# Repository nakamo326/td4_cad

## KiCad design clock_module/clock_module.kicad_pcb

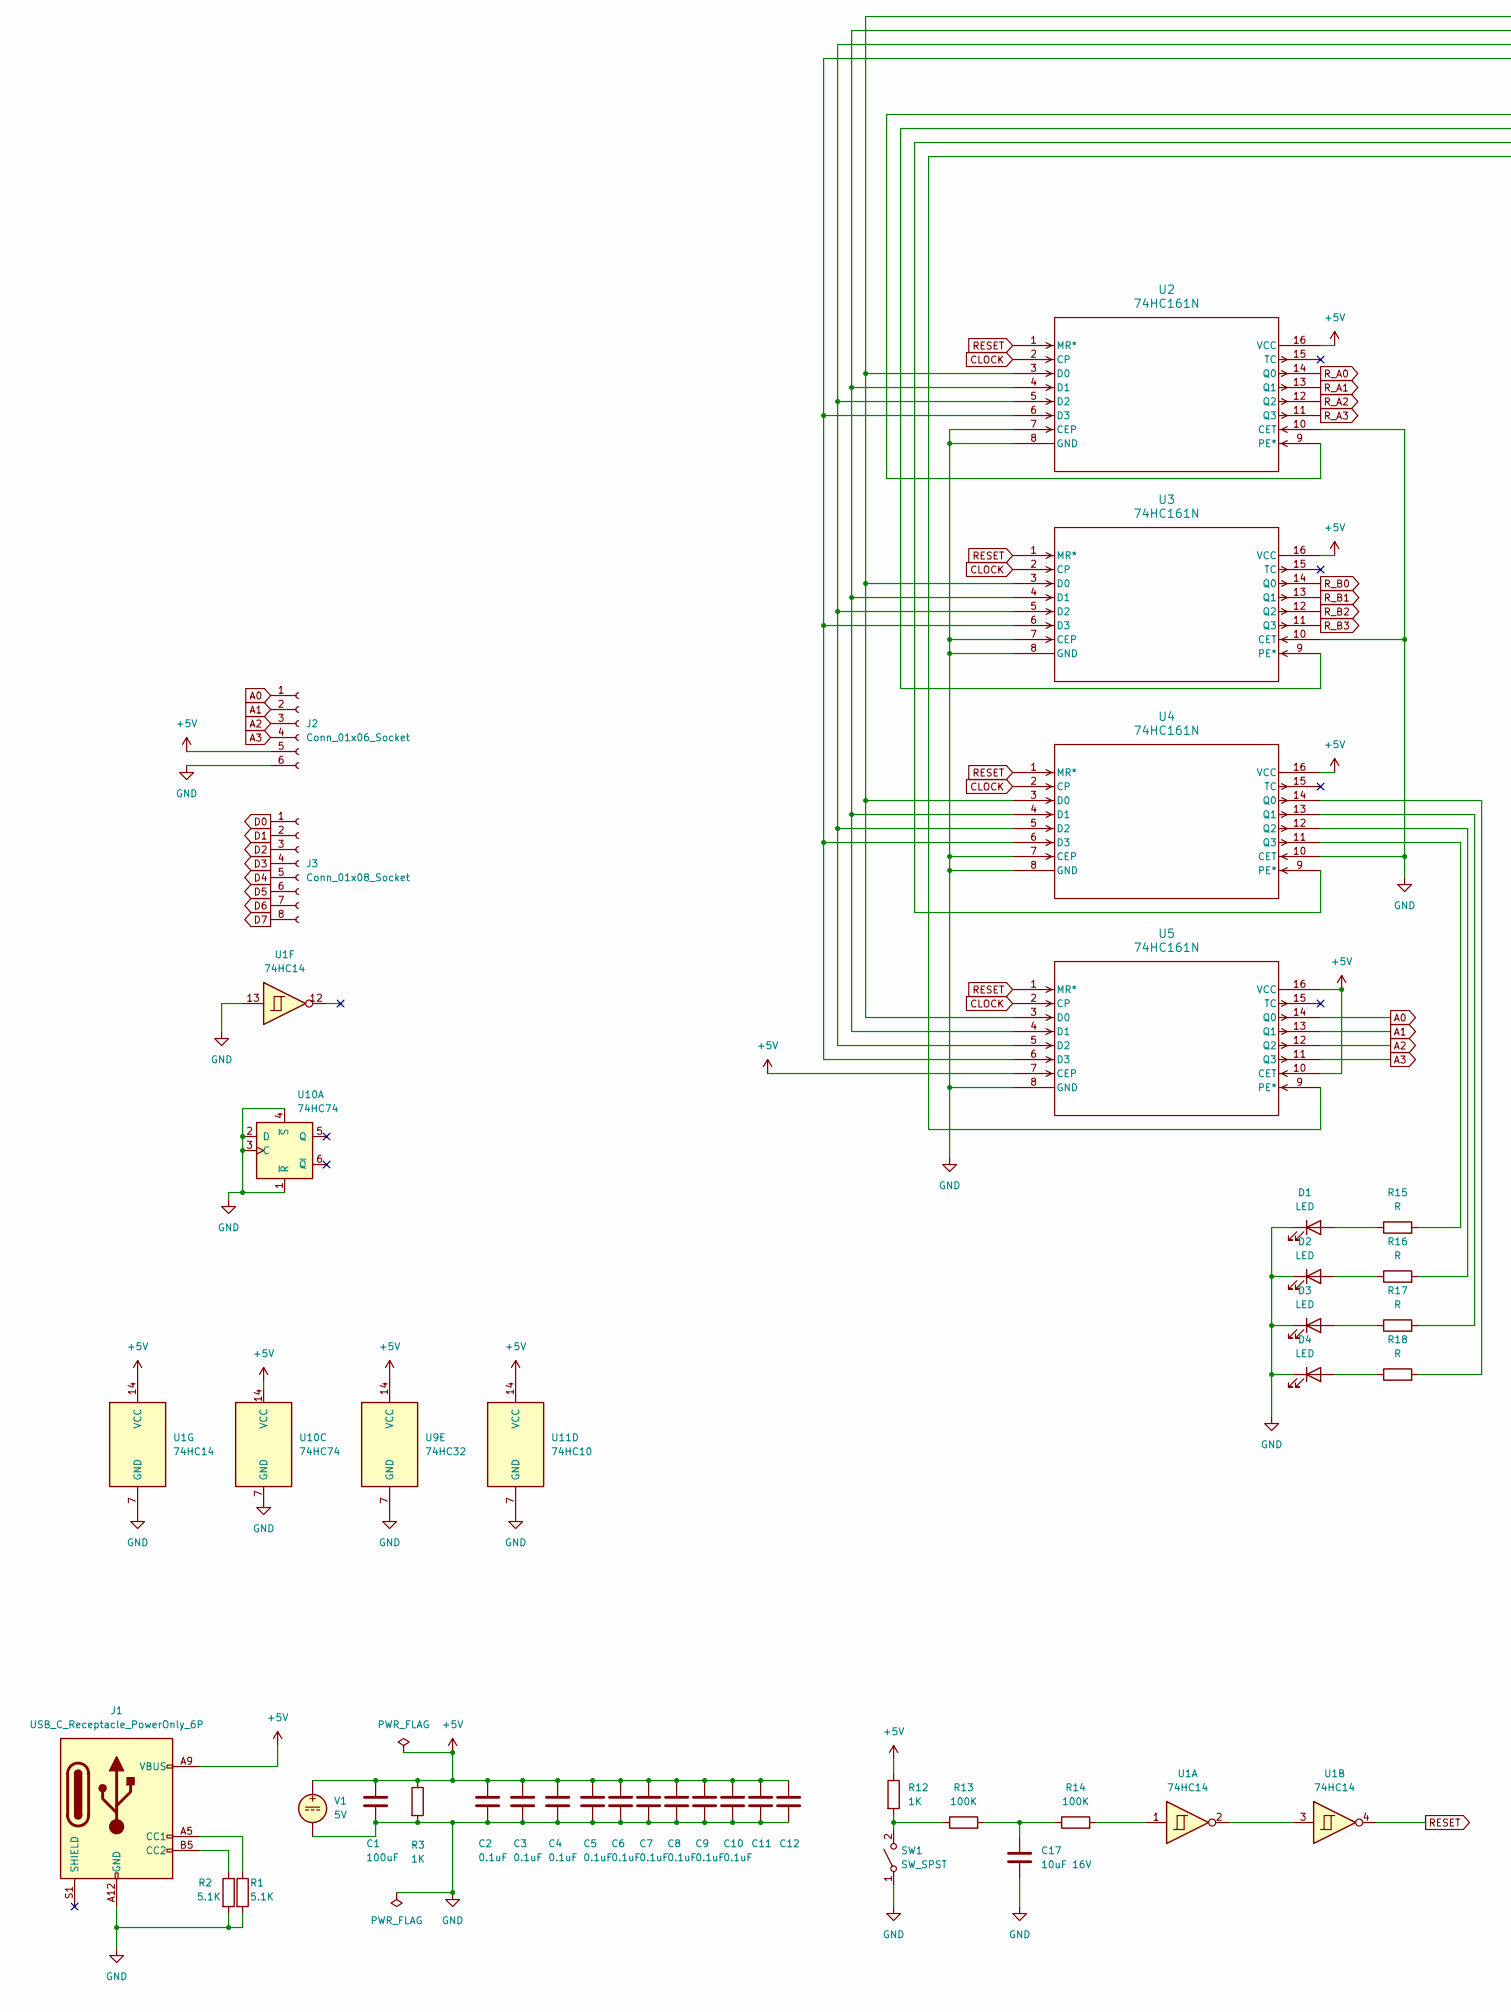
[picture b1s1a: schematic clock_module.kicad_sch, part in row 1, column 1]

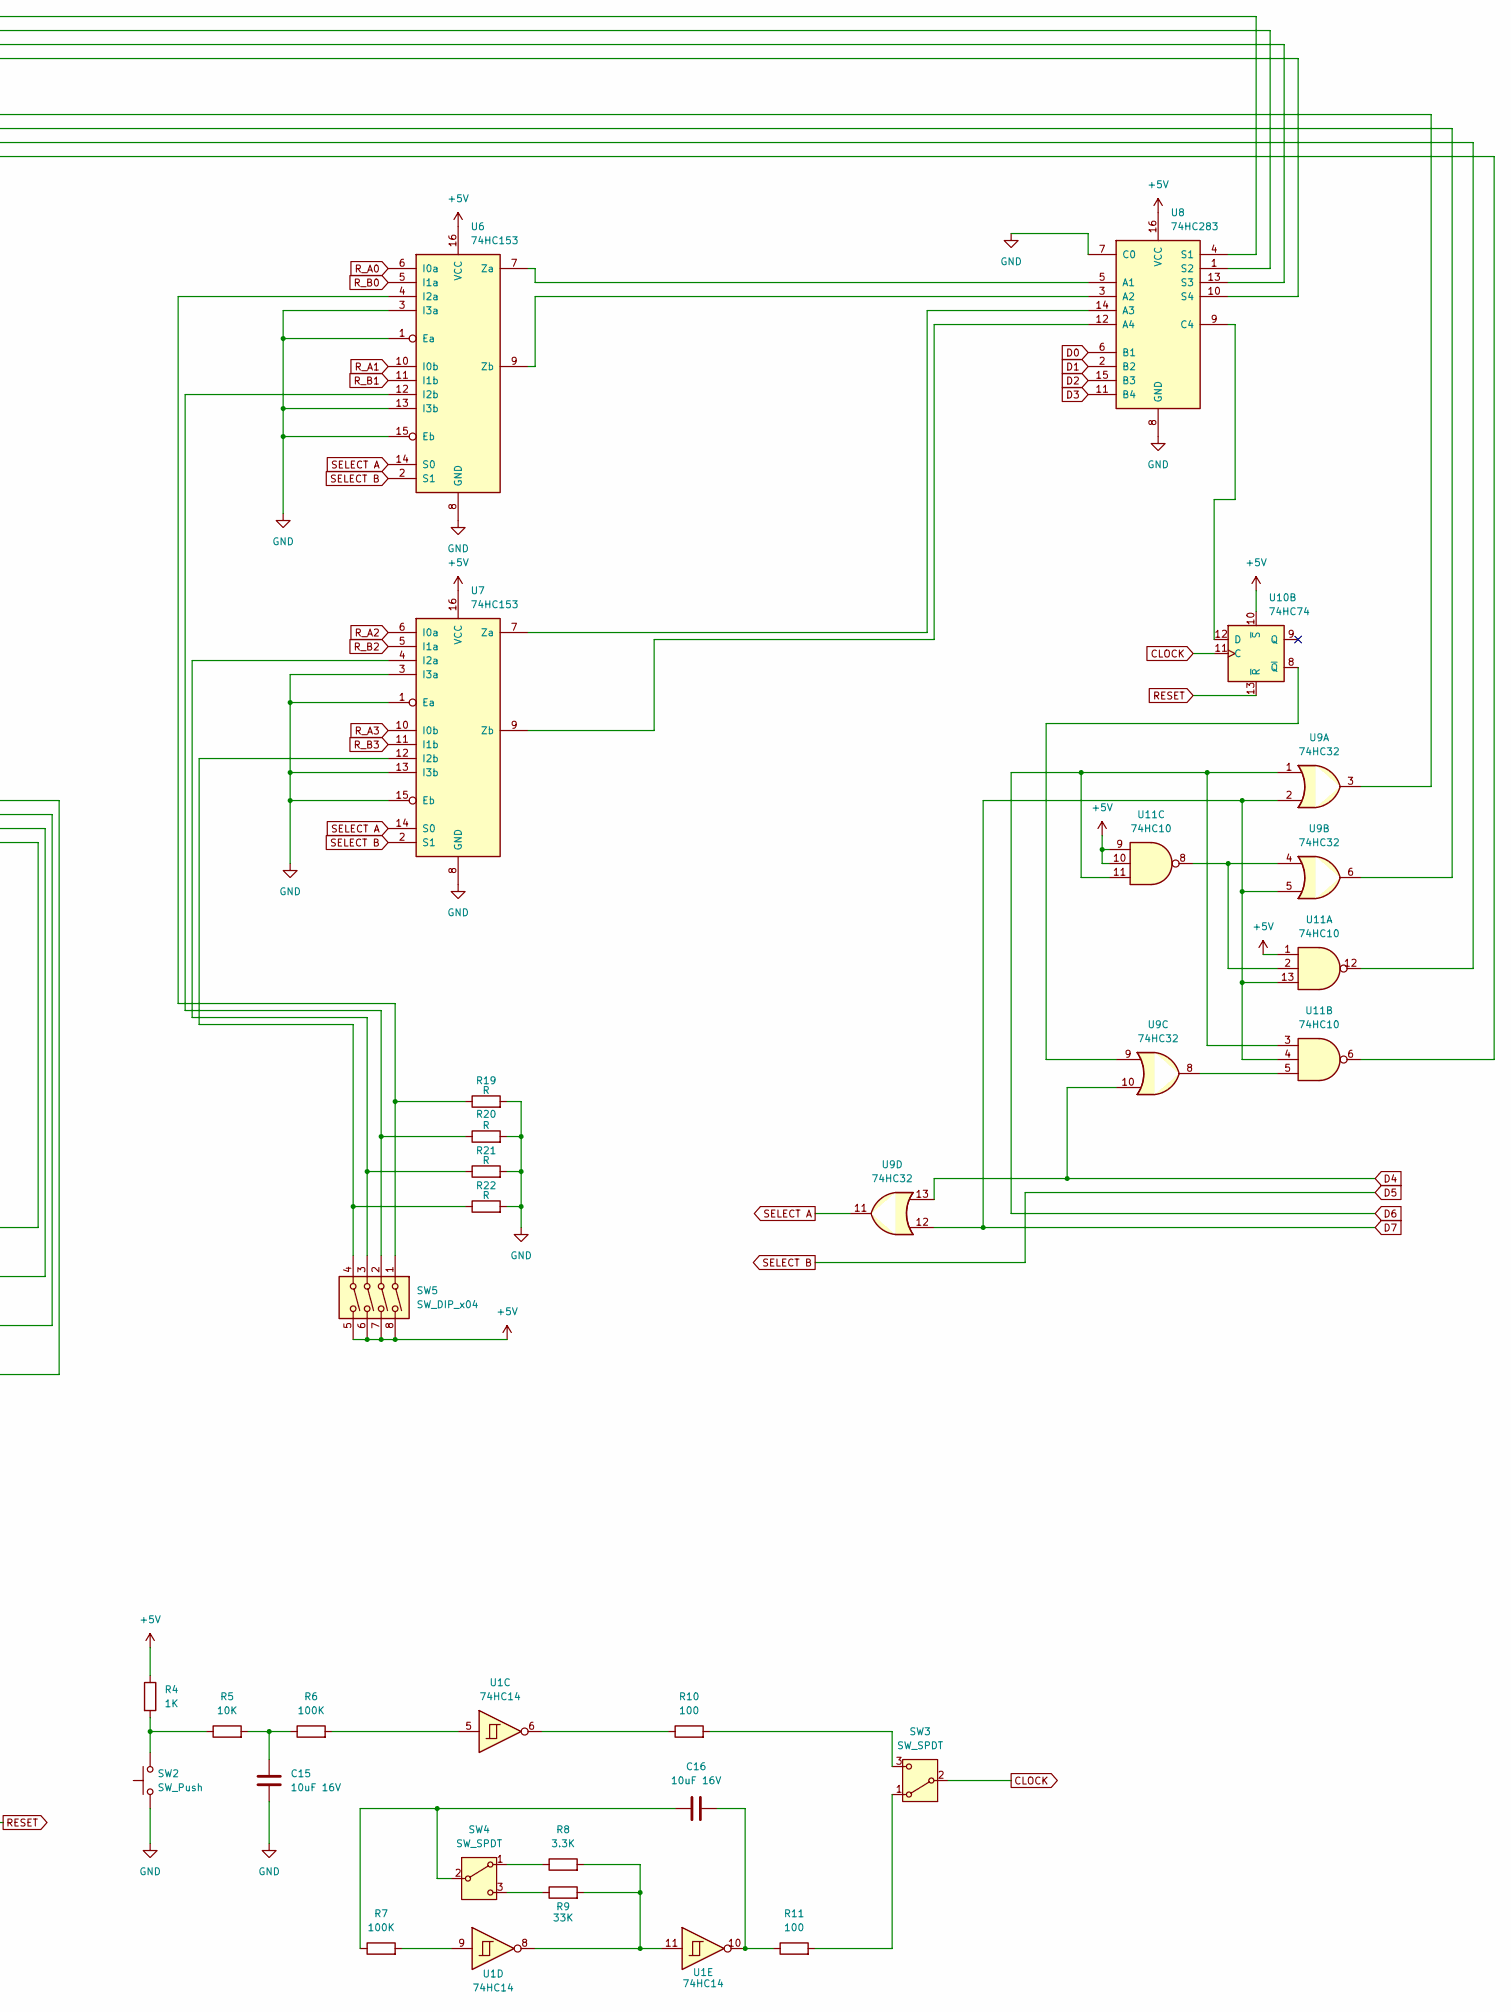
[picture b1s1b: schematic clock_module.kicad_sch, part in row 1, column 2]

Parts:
C1: 100uF; C_Disc_D4.3mm_W1.9mm_P5.00mm
C2, C3, C4, C5, C6, C7, C8, C9, C10, C11, C12: 0.1uF; C_Disc_D4.3mm_W1.9mm_P5.00mm
C15, C16, C17: 10uF 16V; C_Disc_D4.3mm_W1.9mm_P5.00mm
D1, D2, D3, D4: LED; LED_D3.0mm
J1: USB_C_Receptacle_PowerOnly_6P; UJC-HP-3-SMT-TR
J2: Conn_01x06_Socket; PinSocket_1x06_P2.54mm_Horizontal
J3: Conn_01x08_Socket; PinSocket_1x08_P2.54mm_Horizontal
R1, R2: 5.1K; R_Axial_DIN0207_L6.3mm_D2.5mm_P2.54mm_Vertical
R3, R4, R12: 1K; R_Axial_DIN0207_L6.3mm_D2.5mm_P2.54mm_Vertical
R5: 10K; R_Axial_DIN0207_L6.3mm_D2.5mm_P2.54mm_Vertical
R6, R7, R13, R14: 100K; R_Axial_DIN0207_L6.3mm_D2.5mm_P2.54mm_Vertical
R8: 3.3K; R_Axial_DIN0207_L6.3mm_D2.5mm_P2.54mm_Vertical
R9: 33K; R_Axial_DIN0207_L6.3mm_D2.5mm_P2.54mm_Vertical
R10, R11: 100; R_Axial_DIN0207_L6.3mm_D2.5mm_P2.54mm_Vertical
R15, R16, R17, R18, R19, R20, R21, R22: R; R_Axial_DIN0207_L6.3mm_D2.5mm_P2.54mm_Vertical
SW1: SW_SPST; SW_PUSH_6mm
SW2: SW_Push; SW_PUSH_6mm
SW3, SW4: SW_SPDT; SS-12D00G3
SW5: SW_DIP_x04; SW_DIP_SPSTx04_Slide_9.78x12.34mm_W7.62mm_P2.54mm
U1: 74HC14; DIP14_TOS
U2, U3, U4, U5: 74HC161N; 74hc161
U6, U7: 74HC153; SOT38-4_NEX
U8: 74HC283; 74hc283
U9: 74HC32; 74hc32
U10: 74HC74; DIP14_TOS
U11: 74HC10; 74hc10
V1: 5V

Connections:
+5V: C1.1, C2.1, C3.1, C4.1, C5.1, C6.1, C7.1, C8.1, C9.1, C10.1, C11.1, C12.1, J1.A9 (VBUS), J1.B9 (VBUS), J2.5, R3.1, R4.1, R12.1, SW5.5, SW5.6, SW5.7, SW5.8, U1.14 (VCC), U2.16 (VCC), U3.16 (VCC), U4.16 (VCC), U5.7 (CEP), U5.10 (CET), U5.16 (VCC), U6.16 (VCC), U7.16 (VCC), U8.16 (VCC), U9.14 (VCC), U10.10 (~S), U10.14 (VCC), U11.1, U11.9, U11.10, U11.14 (VCC), V1.1
A0: J2.1, U5.14 (Q0)
A1: J2.2, U5.13 (Q1)
A2: J2.3, U5.12 (Q2)
A3: J2.4, U5.11 (Q3)
CLOCK: SW3.2 (B), U2.2 (CP), U3.2 (CP), U4.2 (CP), U5.2 (CP), U10.11 (C)
D0: J3.1, U8.6 (B1)
D1: J3.2, U8.2 (B2)
D2: J3.3, U8.15 (B3)
D3: J3.4, U8.11 (B4)
D4: J3.5, U9.10, U9.13
D5: J3.6, U6.2 (S1), U7.2 (S1)
D6: J3.7, U9.1, U11.3, U11.11
D7: J3.8, U9.2, U9.5, U9.12, U11.4, U11.13
GND: C1.2, C2.2, C3.2, C4.2, C5.2, C6.2, C7.2, C8.2, C9.2, C10.2, C11.2, C12.2, C15.2, C17.2, D1.1 (K), D2.1 (K), D3.1 (K), D4.1 (K), J1.A12 (GND), J1.B12 (GND), J2.6, R1.2, R2.2, R3.2, R19.2, R20.2, R21.2, R22.2, SW1.1 (A), SW2.1, U1.7 (GND), U1.13, U2.7 (CEP), U2.8 (GND), U2.10 (CET), U3.7 (CEP), U3.8 (GND), U3.10 (CET), U4.7 (CEP), U4.8 (GND), U4.10 (CET), U5.8 (GND), U6.1 (Ea), U6.3 (I3a), U6.8 (GND), U6.13 (I3b), U6.15 (Eb), U7.1 (Ea), U7.3 (I3a), U7.8 (GND), U7.13 (I3b), U7.15 (Eb), U8.7 (C0), U8.8 (GND), U9.7 (GND), U10.1 (~R), U10.2 (D), U10.3 (C), U10.4 (~S), U10.7 (GND), U11.7 (GND), V1.2
unnamed: C15.1, R5.2, R6.1
unnamed: C16.2, R11.1, U1.10
unnamed: C17.1, R13.2, R14.1
unnamed: D1.2 (A), R15.1
unnamed: D2.2 (A), R16.1
unnamed: D3.2 (A), R17.1
unnamed: D4.2 (A), R18.1
unnamed: J1.A5 (CC1), R1.1
unnamed: J1.B5 (CC2), R2.1
unnamed: R4.2, R5.1, SW2.2
unnamed: R6.2, U1.5
unnamed: R7.2, U1.9
unnamed: R8.2, R9.2, U1.8, U1.11
unnamed: R10.1, U1.6
unnamed: R14.2, U1.1
unnamed: R12.2, R13.1, SW1.2 (B)
unnamed: R11.2, SW3.1 (A)
unnamed: R10.2, SW3.3 (C)
unnamed: R8.1, SW4.1 (A)
unnamed: C16.1, R7.1, SW4.2 (B)
unnamed: R9.1, SW4.3 (C)
unnamed: U1.2, U1.3
unnamed: U2.3 (D0), U3.3 (D0), U4.3 (D0), U5.3 (D0), U8.4 (S1)
unnamed: U2.4 (D1), U3.4 (D1), U4.4 (D1), U5.4 (D1), U8.1 (S2)
unnamed: U2.5 (D2), U3.5 (D2), U4.5 (D2), U5.5 (D2), U8.13 (S3)
unnamed: U2.6 (D3), U3.6 (D3), U4.6 (D3), U5.6 (D3), U8.10 (S4)
unnamed: U2.9 (PE*), U9.3
unnamed: U3.9 (PE*), U9.6
unnamed: U4.9 (PE*), U11.12
unnamed: R18.2, U4.14 (Q0)
unnamed: R17.2, U4.13 (Q1)
unnamed: R16.2, U4.12 (Q2)
unnamed: R15.2, U4.11 (Q3)
unnamed: U5.9 (PE*), U11.6
unnamed: R19.1, SW5.1, U6.4 (I2a)
unnamed: R20.1, SW5.2, U6.12 (I2b)
unnamed: U6.7 (Za), U8.5 (A1)
unnamed: U6.9 (Zb), U8.3 (A2)
unnamed: R21.1, SW5.3, U7.4 (I2a)
unnamed: R22.1, SW5.4, U7.12 (I2b)
unnamed: U7.7 (Za), U8.14 (A3)
unnamed: U7.9 (Zb), U8.12 (A4)
unnamed: U8.9 (C4), U10.12 (D)
unnamed: U9.9, U10.8 (~Q)
unnamed: U9.4, U11.2, U11.8
unnamed: U9.8, U11.5
RESET: U1.4, U2.1 (MR*), U3.1 (MR*), U4.1 (MR*), U5.1 (MR*), U10.13 (~R)
R_A0: U2.14 (Q0), U6.6 (I0a)
R_A1: U2.13 (Q1), U6.10 (I0b)
R_A2: U2.12 (Q2), U7.6 (I0a)
R_A3: U2.11 (Q3), U7.10 (I0b)
R_B0: U3.14 (Q0), U6.5 (I1a)
R_B1: U3.13 (Q1), U6.11 (I1b)
R_B2: U3.12 (Q2), U7.5 (I1a)
R_B3: U3.11 (Q3), U7.11 (I1b)
SELECT A: U6.14 (S0), U7.14 (S0), U9.11

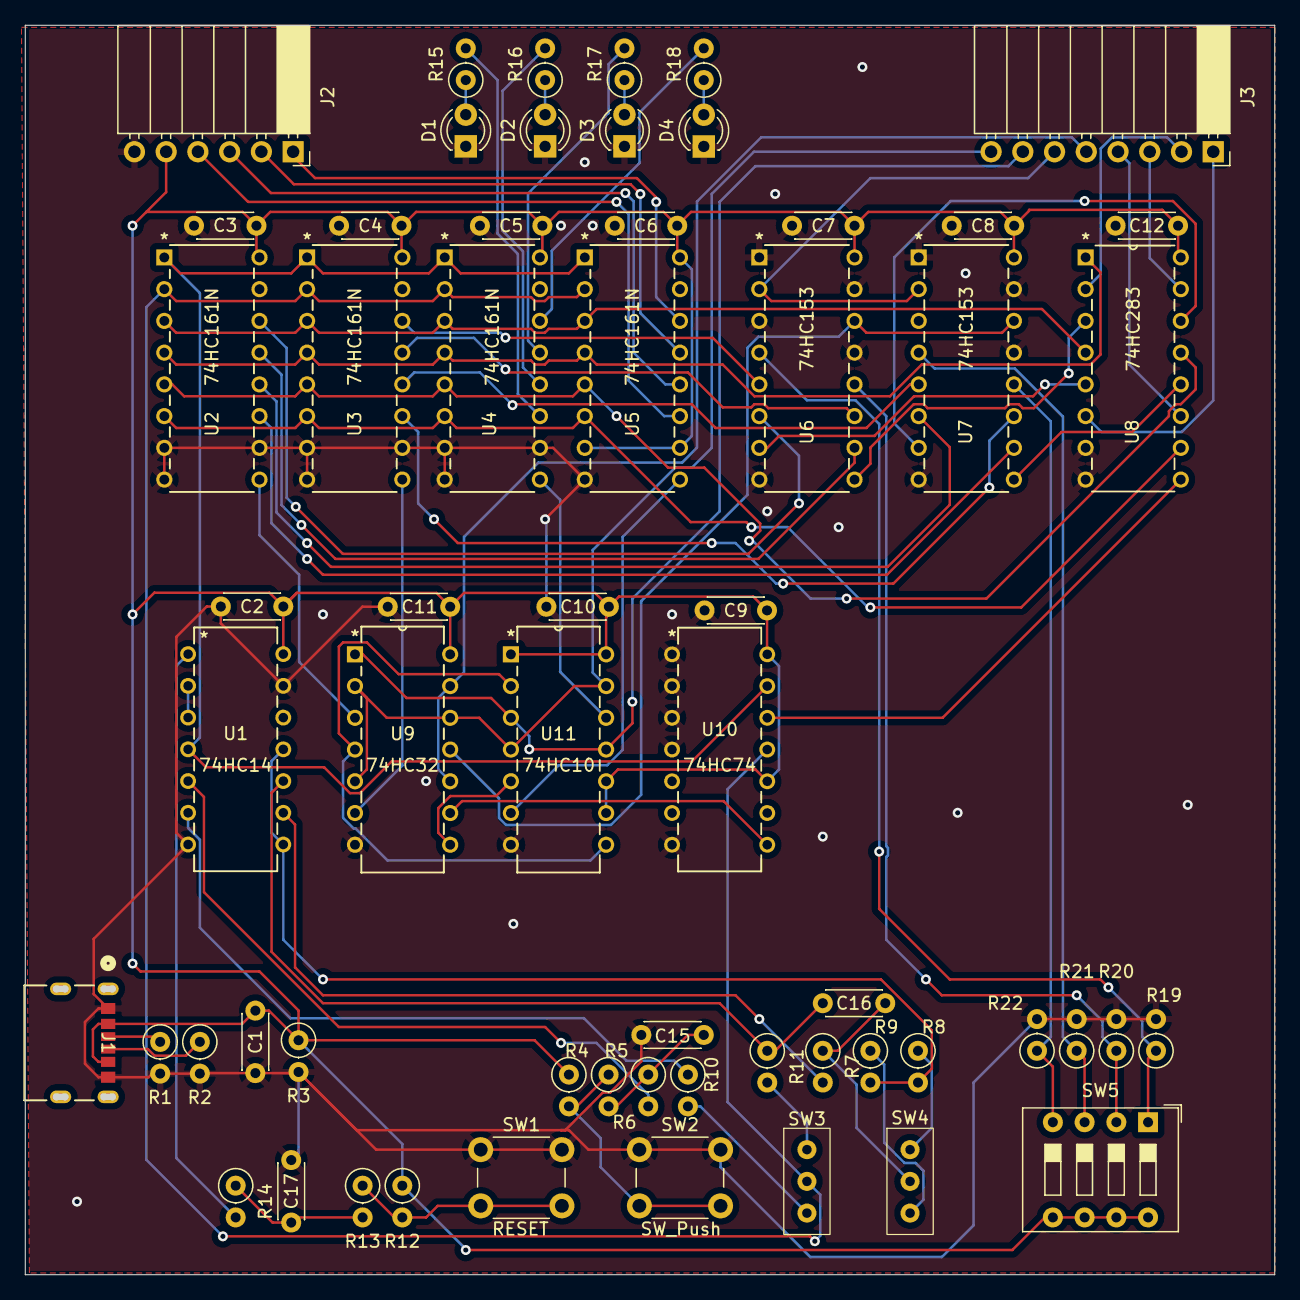
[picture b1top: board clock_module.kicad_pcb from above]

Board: 2 copper layers, 99.5 x 99.5 mm, 60 parts (0 on the bottom side), 71 nets.

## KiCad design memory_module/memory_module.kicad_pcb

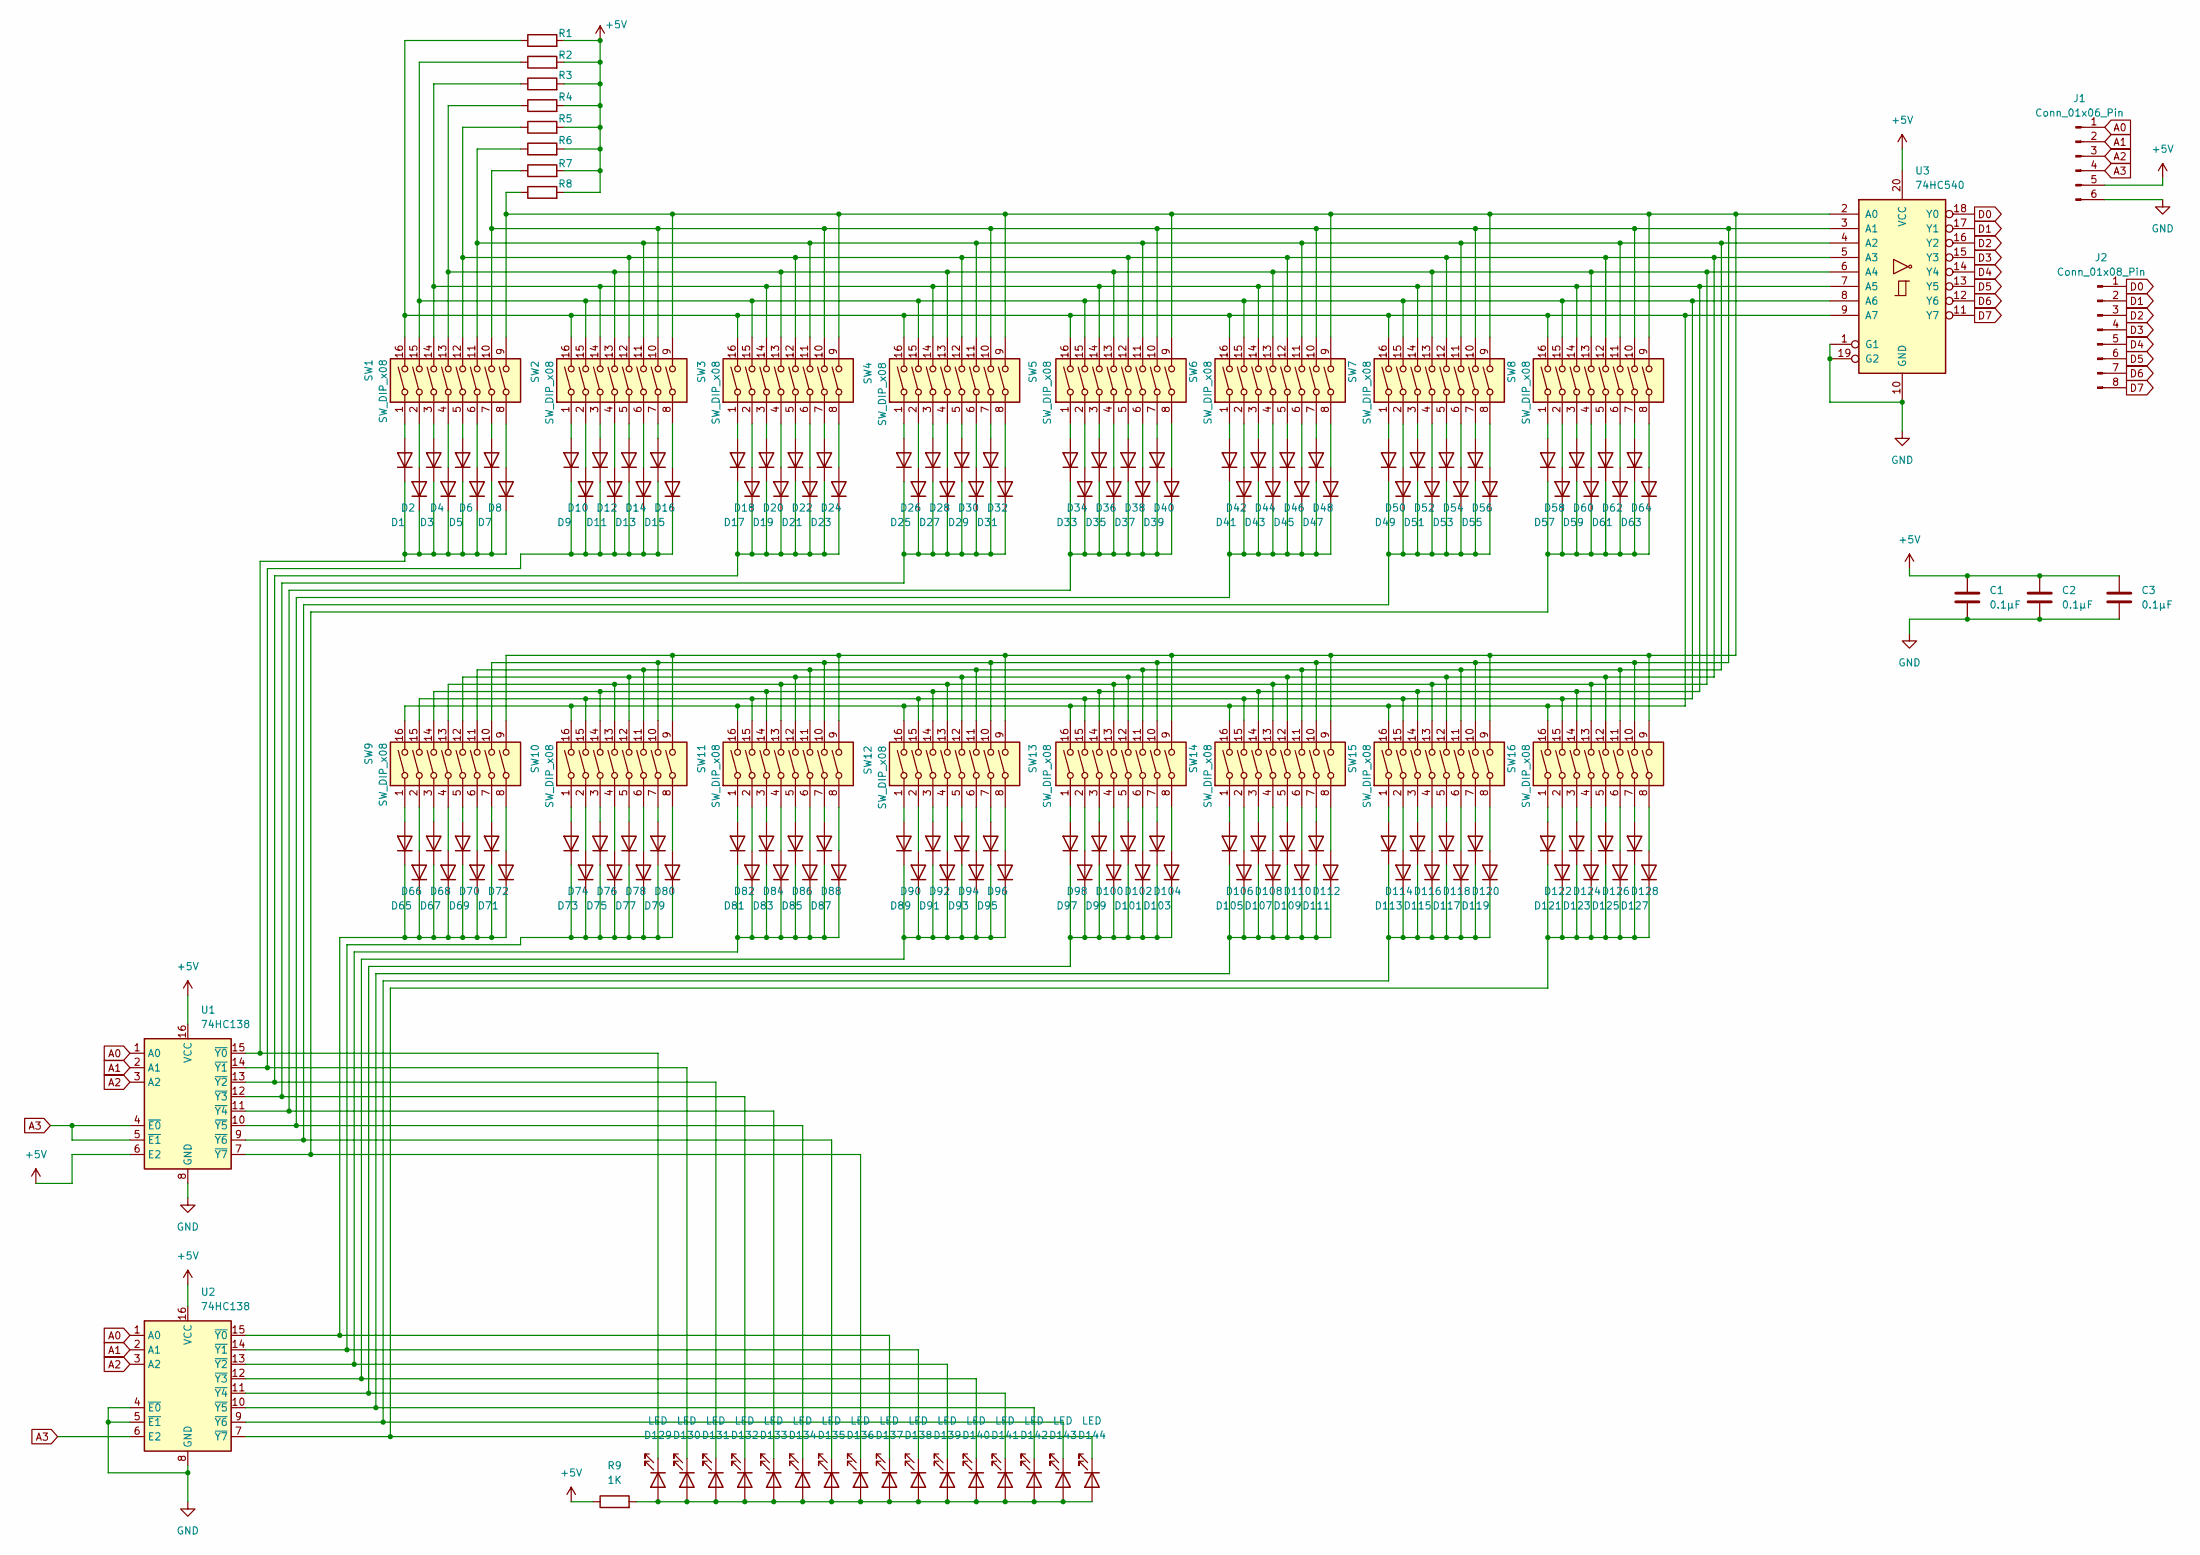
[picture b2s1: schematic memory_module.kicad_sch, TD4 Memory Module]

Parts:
C1, C2, C3: 0.1μF; C_Disc_D4.3mm_W1.9mm_P5.00mm
D1, D2, D3, D4, D5, D6, D7, D8, D9, D10, D11, D12, D13, D14, D15, D16, D17, D18, D19, D20, D21, D22, D23, D24, D25, D26, D27, D28, D29, D30, D31, D32, D33, D34, D35, D36, D37, D38, D39, D40, D41, D42, D43, D44, D45, D46, D47, D48, D49, D50, D51, D52, D53, D54, D55, D56, D57, D58, D59, D60, D61, D62, D63, D64, D65, D66, D67, D68, D69, D70, D71, D72, D73, D74, D75, D76, D77, D78, D79, D80, D81, D82, D83, D84, D85, D86, D87, D88, D89, D90, D91, D92, D93, D94, D95, D96, D97, D98, D99, D100, D101, D102, D103, D104, D105, D106, D107, D108, D109, D110, D111, D112, D113, D114, D115, D116, D117, D118, D119, D120, D121, D122, D123, D124, D125, D126, D127, D128: 1N4148; D_DO-35_SOD27_P2.54mm_Vertical_KathodeUp
D129, D130, D131, D132, D133, D134, D135, D136, D137, D138, D139, D140, D141, D142, D143, D144: LED; LED_1206_3216Metric_Pad1.42x1.75mm_HandSolder
J1: Conn_01x06_Pin; PinHeader_1x06_P2.54mm_Horizontal
J2: Conn_01x08_Pin; PinHeader_1x08_P2.54mm_Horizontal
R1, R2: 10K; R_Axial_DIN0207_L6.3mm_D2.5mm_P2.54mm_Vertical
R3, R4, R5, R6, R7, R8: R; R_Axial_DIN0207_L6.3mm_D2.5mm_P2.54mm_Vertical
R9: 1K; R_Axial_DIN0207_L6.3mm_D2.5mm_P2.54mm_Vertical
SW1, SW2, SW3, SW4, SW5, SW6, SW7, SW8, SW9, SW10, SW11, SW12, SW13, SW14, SW15, SW16: SW_DIP_x08; SW_DIP_SPSTx08_Slide_9.78x22.5mm_W7.62mm_P2.54mm
U1, U2: 74HC138; DIP16_TOS
U3: 74HC540; DIP20_TOS

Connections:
+5V: C1.1, C2.1, C3.1, J1.5, R1.2, R2.2, R3.2, R4.2, R5.2, R6.2, R7.2, R8.2, R9.1, U1.6 (E2), U1.16 (VCC), U2.16 (VCC), U3.20 (VCC)
A0: J1.1, U1.1 (A0), U2.1 (A0)
A1: J1.2, U1.2 (A1), U2.2 (A1)
A2: J1.3, U1.3 (A2), U2.3 (A2)
A3: J1.4, U1.4 (~E0), U1.5 (~E1), U2.6 (E2)
D0: J2.1, U3.18 (Y0)
D1: J2.2, U3.17 (Y1)
D2: J2.3, U3.16 (Y2)
D3: J2.4, U3.15 (Y3)
D4: J2.5, U3.14 (Y4)
D5: J2.6, U3.13 (Y5)
D6: J2.7, U3.12 (Y6)
D7: J2.8, U3.11 (Y7)
GND: C1.2, C2.2, C3.2, J1.6, U1.8 (GND), U2.4 (~E0), U2.5 (~E1), U2.8 (GND), U3.1 (G1), U3.10 (GND), U3.19 (G2)
unnamed: D1.2 (A), SW1.1
unnamed: D1.1 (K), D2.1 (K), D3.1 (K), D4.1 (K), D5.1 (K), D6.1 (K), D7.1 (K), D8.1 (K), D129.1 (K), U1.15 (~Y0)
unnamed: D2.2 (A), SW1.2
unnamed: D3.2 (A), SW1.3
unnamed: D4.2 (A), SW1.4
unnamed: D5.2 (A), SW1.5
unnamed: D6.2 (A), SW1.6
unnamed: D7.2 (A), SW1.7
unnamed: D8.2 (A), SW1.8
unnamed: D9.2 (A), SW2.1
unnamed: D10.2 (A), SW2.2
unnamed: D9.1 (K), D10.1 (K), D11.1 (K), D12.1 (K), D13.1 (K), D14.1 (K), D15.1 (K), D16.1 (K), D130.1 (K), U1.14 (~Y1)
unnamed: D11.2 (A), SW2.3
unnamed: D12.2 (A), SW2.4
unnamed: D13.2 (A), SW2.5
unnamed: D14.2 (A), SW2.6
unnamed: D15.2 (A), SW2.7
unnamed: D16.2 (A), SW2.8
unnamed: D17.2 (A), SW3.1
unnamed: D18.2 (A), SW3.2
unnamed: D19.2 (A), SW3.3
unnamed: D20.2 (A), SW3.4
unnamed: D21.2 (A), SW3.5
unnamed: D22.2 (A), SW3.6
unnamed: D23.2 (A), SW3.7
unnamed: D24.2 (A), SW3.8
unnamed: D25.2 (A), SW4.1
unnamed: D26.2 (A), SW4.2
unnamed: D27.2 (A), SW4.3
unnamed: D28.2 (A), SW4.4
unnamed: D29.2 (A), SW4.5
unnamed: D30.2 (A), SW4.6
unnamed: D31.2 (A), SW4.7
unnamed: D32.2 (A), SW4.8
unnamed: D33.2 (A), SW5.1
unnamed: D34.2 (A), SW5.2
unnamed: D35.2 (A), SW5.3
unnamed: D36.2 (A), SW5.4
unnamed: D37.2 (A), SW5.5
unnamed: D38.2 (A), SW5.6
unnamed: D39.2 (A), SW5.7
unnamed: D40.2 (A), SW5.8
unnamed: D41.2 (A), SW6.1
unnamed: D42.2 (A), SW6.2
unnamed: D43.2 (A), SW6.3
unnamed: D44.2 (A), SW6.4
unnamed: D45.2 (A), SW6.5
unnamed: D46.2 (A), SW6.6
unnamed: D47.2 (A), SW6.7
unnamed: D48.2 (A), SW6.8
unnamed: D49.2 (A), SW7.1
unnamed: D50.2 (A), SW7.2
unnamed: D51.2 (A), SW7.3
unnamed: D52.2 (A), SW7.4
unnamed: D53.2 (A), SW7.5
unnamed: D54.2 (A), SW7.6
unnamed: D55.2 (A), SW7.7
unnamed: D56.2 (A), SW7.8
unnamed: D57.2 (A), SW8.1
unnamed: D58.2 (A), SW8.2
unnamed: D59.2 (A), SW8.3
unnamed: D60.2 (A), SW8.4
unnamed: D61.2 (A), SW8.5
unnamed: D62.2 (A), SW8.6
unnamed: D63.2 (A), SW8.7
unnamed: D64.2 (A), SW8.8
unnamed: D65.2 (A), SW9.1
unnamed: D66.2 (A), SW9.2
unnamed: D67.2 (A), SW9.3
unnamed: D68.2 (A), SW9.4
unnamed: D69.2 (A), SW9.5
unnamed: D70.2 (A), SW9.6
unnamed: D71.2 (A), SW9.7
unnamed: D72.2 (A), SW9.8
unnamed: D73.2 (A), SW10.1
unnamed: D74.2 (A), SW10.2
unnamed: D75.2 (A), SW10.3
unnamed: D76.2 (A), SW10.4
unnamed: D77.2 (A), SW10.5
unnamed: D78.2 (A), SW10.6
unnamed: D79.2 (A), SW10.7
unnamed: D80.2 (A), SW10.8
unnamed: D81.2 (A), SW11.1
unnamed: D82.2 (A), SW11.2
unnamed: D83.2 (A), SW11.3
unnamed: D84.2 (A), SW11.4
unnamed: D85.2 (A), SW11.5
unnamed: D86.2 (A), SW11.6
unnamed: D87.2 (A), SW11.7
unnamed: D88.2 (A), SW11.8
unnamed: D89.2 (A), SW12.1
unnamed: D90.2 (A), SW12.2
unnamed: D91.2 (A), SW12.3
unnamed: D92.2 (A), SW12.4
unnamed: D93.2 (A), SW12.5
unnamed: D94.2 (A), SW12.6
unnamed: D95.2 (A), SW12.7
unnamed: D96.2 (A), SW12.8
unnamed: D97.2 (A), SW13.1
unnamed: D98.2 (A), SW13.2
unnamed: D99.2 (A), SW13.3
unnamed: D100.2 (A), SW13.4
unnamed: D97.1 (K), D98.1 (K), D99.1 (K), D100.1 (K), D101.1 (K), D102.1 (K), D103.1 (K), D104.1 (K), D141.1 (K), U2.11 (~Y4)
unnamed: D101.2 (A), SW13.5
unnamed: D102.2 (A), SW13.6
unnamed: D103.2 (A), SW13.7
unnamed: D104.2 (A), SW13.8
unnamed: D105.2 (A), SW14.1
unnamed: D105.1 (K), D106.1 (K), D107.1 (K), D108.1 (K), D109.1 (K), D110.1 (K), D111.1 (K), D112.1 (K), D142.1 (K), U2.10 (~Y5)
unnamed: D106.2 (A), SW14.2
unnamed: D107.2 (A), SW14.3
unnamed: D108.2 (A), SW14.4
unnamed: D109.2 (A), SW14.5
unnamed: D110.2 (A), SW14.6
unnamed: D111.2 (A), SW14.7
unnamed: D112.2 (A), SW14.8
unnamed: D113.2 (A), SW15.1
unnamed: D113.1 (K), D114.1 (K), D115.1 (K), D116.1 (K), D117.1 (K), D118.1 (K), D119.1 (K), D120.1 (K), D143.1 (K), U2.9 (~Y6)
unnamed: D114.2 (A), SW15.2
unnamed: D115.2 (A), SW15.3
unnamed: D116.2 (A), SW15.4
unnamed: D117.2 (A), SW15.5
unnamed: D118.2 (A), SW15.6
unnamed: D119.2 (A), SW15.7
unnamed: D120.2 (A), SW15.8
unnamed: D121.2 (A), SW16.1
unnamed: D121.1 (K), D122.1 (K), D123.1 (K), D124.1 (K), D125.1 (K), D126.1 (K), D127.1 (K), D128.1 (K), D144.1 (K), U2.7 (~Y7)
unnamed: D122.2 (A), SW16.2
unnamed: D123.2 (A), SW16.3
unnamed: D124.2 (A), SW16.4
unnamed: D125.2 (A), SW16.5
unnamed: D126.2 (A), SW16.6
unnamed: D127.2 (A), SW16.7
unnamed: D128.2 (A), SW16.8
unnamed: D129.2 (A), D130.2 (A), D131.2 (A), D132.2 (A), D133.2 (A), D134.2 (A), D135.2 (A), D136.2 (A), D137.2 (A), D138.2 (A), D139.2 (A), D140.2 (A), D141.2 (A), D142.2 (A), D143.2 (A), D144.2 (A), R9.2
unnamed: D17.1 (K), D18.1 (K), D19.1 (K), D20.1 (K), D21.1 (K), D22.1 (K), D23.1 (K), D24.1 (K), D131.1 (K), U1.13 (~Y2)
unnamed: D25.1 (K), D26.1 (K), D27.1 (K), D28.1 (K), D29.1 (K), D30.1 (K), D31.1 (K), D32.1 (K), D132.1 (K), U1.12 (~Y3)
unnamed: D33.1 (K), D34.1 (K), D35.1 (K), D36.1 (K), D37.1 (K), D38.1 (K), D39.1 (K), D40.1 (K), D133.1 (K), U1.11 (~Y4)
unnamed: D41.1 (K), D42.1 (K), D43.1 (K), D44.1 (K), D45.1 (K), D46.1 (K), D47.1 (K), D48.1 (K), D134.1 (K), U1.10 (~Y5)
unnamed: D49.1 (K), D50.1 (K), D51.1 (K), D52.1 (K), D53.1 (K), D54.1 (K), D55.1 (K), D56.1 (K), D135.1 (K), U1.9 (~Y6)
unnamed: D57.1 (K), D58.1 (K), D59.1 (K), D60.1 (K), D61.1 (K), D62.1 (K), D63.1 (K), D64.1 (K), D136.1 (K), U1.7 (~Y7)
unnamed: D65.1 (K), D66.1 (K), D67.1 (K), D68.1 (K), D69.1 (K), D70.1 (K), D71.1 (K), D72.1 (K), D137.1 (K), U2.15 (~Y0)
unnamed: D73.1 (K), D74.1 (K), D75.1 (K), D76.1 (K), D77.1 (K), D78.1 (K), D79.1 (K), D80.1 (K), D138.1 (K), U2.14 (~Y1)
unnamed: D81.1 (K), D82.1 (K), D83.1 (K), D84.1 (K), D85.1 (K), D86.1 (K), D87.1 (K), D88.1 (K), D139.1 (K), U2.13 (~Y2)
unnamed: D89.1 (K), D90.1 (K), D91.1 (K), D92.1 (K), D93.1 (K), D94.1 (K), D95.1 (K), D96.1 (K), D140.1 (K), U2.12 (~Y3)
unnamed: R8.1, SW1.9, SW2.9, SW3.9, SW4.9, SW5.9, SW6.9, SW7.9, SW8.9, SW9.9, SW10.9, SW11.9, SW12.9, SW13.9, SW14.9, SW15.9, SW16.9, U3.2 (A0)
unnamed: R7.1, SW1.10, SW2.10, SW3.10, SW4.10, SW5.10, SW6.10, SW7.10, SW8.10, SW9.10, SW10.10, SW11.10, SW12.10, SW13.10, SW14.10, SW15.10, SW16.10, U3.3 (A1)
unnamed: R6.1, SW1.11, SW2.11, SW3.11, SW4.11, SW5.11, SW6.11, SW7.11, SW8.11, SW9.11, SW10.11, SW11.11, SW12.11, SW13.11, SW14.11, SW15.11, SW16.11, U3.4 (A2)
unnamed: R5.1, SW1.12, SW2.12, SW3.12, SW4.12, SW5.12, SW6.12, SW7.12, SW8.12, SW9.12, SW10.12, SW11.12, SW12.12, SW13.12, SW14.12, SW15.12, SW16.12, U3.5 (A3)
unnamed: R4.1, SW1.13, SW2.13, SW3.13, SW4.13, SW5.13, SW6.13, SW7.13, SW8.13, SW9.13, SW10.13, SW11.13, SW12.13, SW13.13, SW14.13, SW15.13, SW16.13, U3.6 (A4)
unnamed: R3.1, SW1.14, SW2.14, SW3.14, SW4.14, SW5.14, SW6.14, SW7.14, SW8.14, SW9.14, SW10.14, SW11.14, SW12.14, SW13.14, SW14.14, SW15.14, SW16.14, U3.7 (A5)
unnamed: R2.1, SW1.15, SW2.15, SW3.15, SW4.15, SW5.15, SW6.15, SW7.15, SW8.15, SW9.15, SW10.15, SW11.15, SW12.15, SW13.15, SW14.15, SW15.15, SW16.15, U3.8 (A6)
unnamed: R1.1, SW1.16, SW2.16, SW3.16, SW4.16, SW5.16, SW6.16, SW7.16, SW8.16, SW9.16, SW10.16, SW11.16, SW12.16, SW13.16, SW14.16, SW15.16, SW16.16, U3.9 (A7)

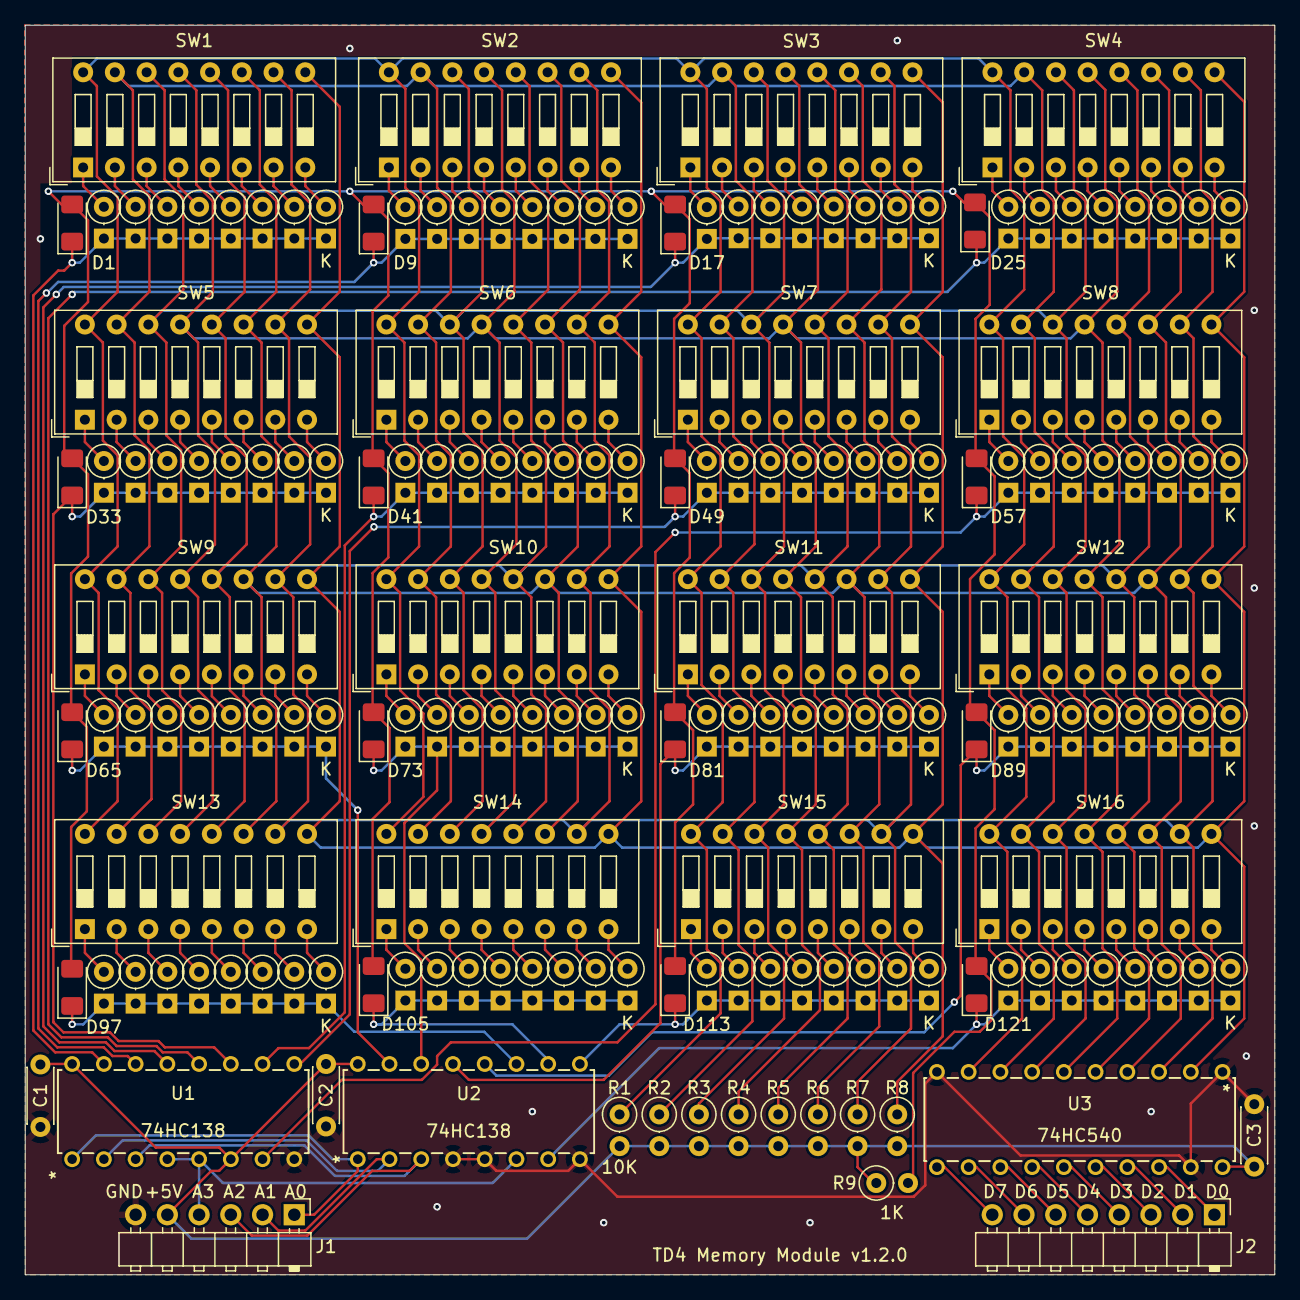
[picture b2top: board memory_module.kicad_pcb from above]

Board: 2 copper layers, 100.0 x 100.0 mm, 177 parts (0 on the bottom side), 167 nets.

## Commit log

2024-11-09 メモリ用の新しいKiCadプロジェクトを追加
2024-11-09 適当に部品を配置
2024-11-09 ICのフットプリントを追加
2024-11-09 回路図進めた
2024-11-10 回路図にコネクターを追加
2024-11-10 ピンヘッダーにフットプリントを追加
2024-11-10 コネクタを配置
2024-11-10 デザインルールを設定
2024-11-10 自動バックアップを停止
2024-11-10 wip: 配置調整
2024-11-10 フットプリント位置調整
2024-11-10 PCBを作成
2024-11-10 ガーバーファイル作成
2024-11-11 pcbをデザイン変更
2024-11-11 clockのプロジェクトを追加
2024-11-13 フットプリント追加
2024-11-17 とりあえず配線した、美しくはない
2024-11-18 電源回路wip
2024-11-21 位置調整wip
2024-12-19 74HC138Nのenableを修正
2024-12-24 フットプリントを修正
2024-12-24 クロック、リセット回路の基盤設計
2024-12-26 パスコンwip
2024-12-27 パスコン追加
2024-12-29 output gerber file
2025-01-05 電源位置変更
2025-01-05 ICをライブラリに追加
2025-01-05 IC追加
2025-01-06 回路図いったん完成
2025-01-06 シンボル、ラベルを修正
2025-01-06 回路図からPCB更新
2025-01-22 コネクタを平面に変更
2025-01-22 コネクタ位置調整
2025-05-22 add: 配線
